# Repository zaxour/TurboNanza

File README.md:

# TurboNanza

***NOTE: I will provide support for Turbonanza if you purchased from:

My Ko-Fi Store: https://ko-fi.com/s/4d0de1c0ac
VideoGamePerfection (EU): https://videogameperfection.com/products/turbonanza-pcengine-turbografx/

If you purchased from AliExpress, I cannot provide support as it looks like they changed the design and did not publish the details.

***

[PC Engine Shuttle Installation Instructions](/images/shuttle/readme.md)

[PC Engine/Turbo Duo Installation Instructions](/images/duo/readme.md)

An internal RGB, S-Video, Composite video and Audio modification for the Turbografx 16, PCEngine and CoreGrafx. As of Revision C, support has been added for audio from the Turbo Everdrive Pro.

Design is KiCad format and all files necessary to open the design and have it fabricated are present within the archive.

Installation Method (WORK IN PROGRESS!!):

PINOUT (For reference/Non-Expansion-Port Installs):

## Step 1 - Remove the resistors for Luma, R-Y, B-Y, and Burst
### PC Engine & CoreGrafx

Remove resistors R134, R137, R138 and R156 

### TurboGrafx 16
Remove resistors R130-R132 and R134

### SuperGrafx
Remove resistors R164-167

## Step 2 - Disconnect CVBS pin from original circuit
### PC Engine & CoreGrafx
Remove resistor R145 (20 ohms)

### TurboGrafx 16
Remove resistor R127 (20 ohms)

### SuperGrafx
Remove resistor R147 

## Step 3 - Install TurboNanza
### PC Engine & CoreGrafx
Solder the TurboNanza over the expansion port pins as shown.

### TurboGrafx16
Solder the TurboNanza over the expansion port pins as shown.

### SuperGrafx
Prepare the flex cable by tinning the pads as shown.

Solder the TurboNanza to the flex cable as shown. It's recommended to verify continuity. Place some kapton/polyimide tape over the exposed solder pads on the bottom of the flex cable to avoid shorting to the shielding.

Solder the TurboNanza/Flex Cable combo over the expansion port pins as shown (ignore 4 wires at this time).

## Step 4 - Solder S-Video connections

**When soldering the Y/B-Y/R-Y/Burst wires, try to use as close to the exact same length of wire as possible to maintain proper phase shift!**

### PC Engine & CoreGrafx
Solder wires from the points shown to the pads on TurboNanza
(Do not remove R141, as previously directed. The Color Burst trace runs underneath and can easily sever. Leave R141 on and solder directly to the resistor pad)

### TurboGrafx 16
Solder wires from the points shown to the pads on TurboNanza

### SuperGrafx
Solder wires from the points shown to the pads on TurboNanza

## Step 5 - Attach the DIN to the main board
### PC Engine
Kits sold after 8/15/2023 now include a mounting board for the PCEngine. It is recommended to secure with two size M2 or 2-56 bolts/washers to allow for easy positioning.

Position the mount and loosely secure with screws/washers. The board may also be soldered - kapton/polyimide tape is recommended to position the board.

Place the DIN in the slot, and solder around the sides.

Solder the DIN FFC adapter to the DIN. Please make sure the "THIS SIDE TOP" text is visible before soldering, as it indicates which side is top.

### CoreGrafx
First, remove C162 (AC coupling capacitor for composite video - no longer necessary)

Scrape the solder mask off the copper on the left and right edges of the original DIN footprint as shown.

Solder the supplied mounting board to the mainboard.

Solder the DIN FFC adapter to the DIN. Please make sure the "THIS SIDE TOP" text is visible before soldering, as it indicates which side is top.

### TurboGrafx16
Solder the mounting board using the plated through holes for the RF modulator. Align the DIN on the mounting board such that it aligns with the console shell opening and solder in place.

### SuperGrafx
Remove the original DIN and scrape the soldermask approximately as shown.

Solder the mounting board as shown, aligning the center hole with the two ground through holes.

Mount the DIN and DIN board to the mount board.

## Step 6 - RF Shielding and Case trimming
### PC Engine
On the bottom shell of the case, trim the 2 ribs where the expansion port opening sits. Do not re-install the original shielding. If your PC Engine has shielding that has two tabs that solder close to the EXP port pins, you will need to run a wire to where the shielding originally terminated.

### CoreGrafx
Trim the RF shield such that the metal lip is not contacting the TurboNanza.

Like the PC Engine, trim the 2 ribs on the bottom shell where the expansion port opening is.

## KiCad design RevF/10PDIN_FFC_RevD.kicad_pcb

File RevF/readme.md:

Turbonanza Revision F

"DecaDIN" files are the smaller interface board meant for PC Engine and CoreGrafx consoles.

"10PDIN" is for all other systems

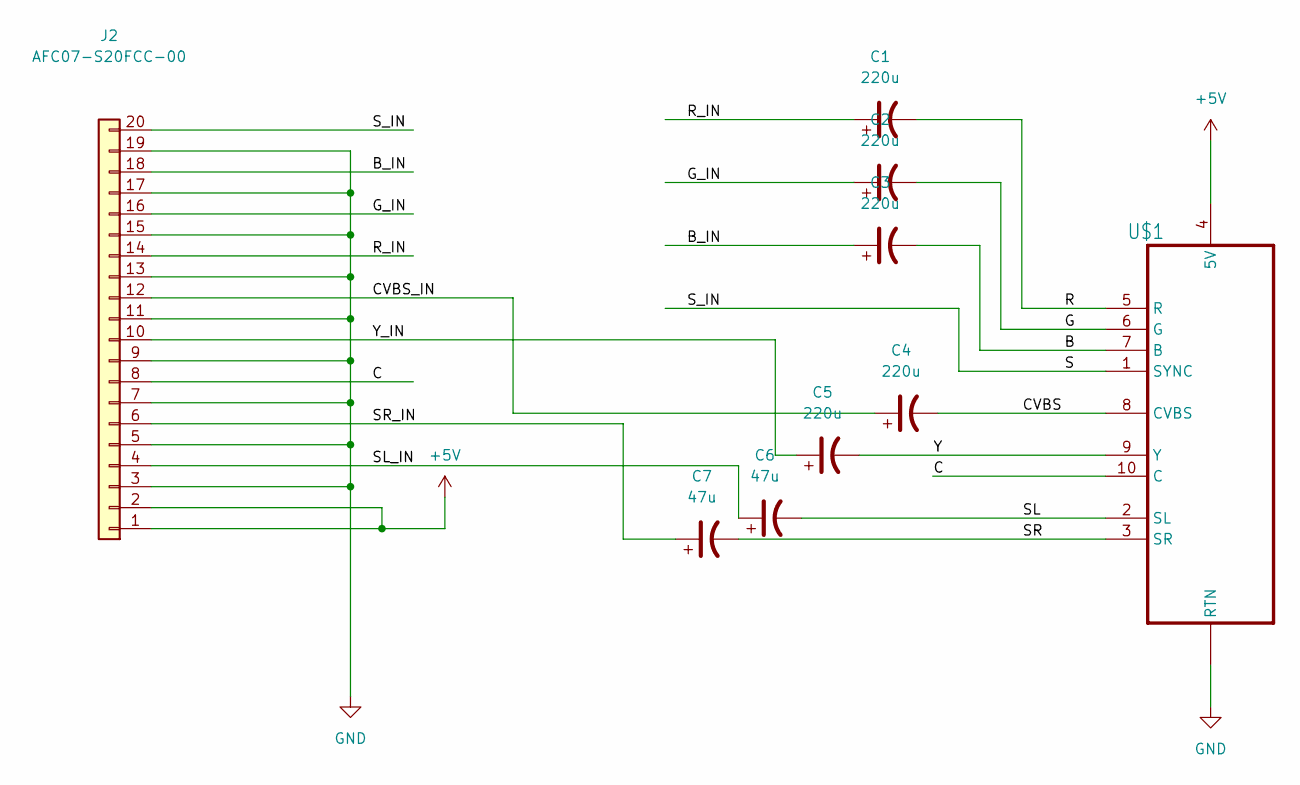
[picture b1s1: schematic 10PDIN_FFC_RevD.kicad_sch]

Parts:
C1, C2, C3, C4, C5: 220u; CP_EIA-3528-15_AVX-H
C6, C7: 47u; CP_EIA-3216-18_Kemet-A
J2: AFC07-S20FCC-00; Jushuo_AFC07-S20FCC-00
U$1: SATURN_10PDIN; CUI_MD-100SM

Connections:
+5V: J2.1, J2.2, U$1.4 (5V)
/B: C3.2, U$1.7 (B)
/B_IN: C3.1, J2.18
/C: J2.8, U$1.10 (C)
/CVBS: C4.2, U$1.8 (CVBS)
/CVBS_IN: C4.1, J2.12
/G: C2.2, U$1.6 (G)
/G_IN: C2.1, J2.16
/R: C1.2, U$1.5 (R)
/R_IN: C1.1, J2.14
/S: J2.20, U$1.1 (SYNC)
/SL: C6.2, U$1.2 (SL)
/SL_IN: C6.1, J2.4
/SR: C7.2, U$1.3 (SR)
/SR_IN: C7.1, J2.6
/Y: C5.2, U$1.9 (Y)
/Y_IN: C5.1, J2.10
GND: J2.3, J2.5, J2.7, J2.9, J2.11, J2.13, J2.15, J2.17, J2.19, U$1.S1 (RTN), U$1.S2 (RTN), U$1.S3 (RTN)

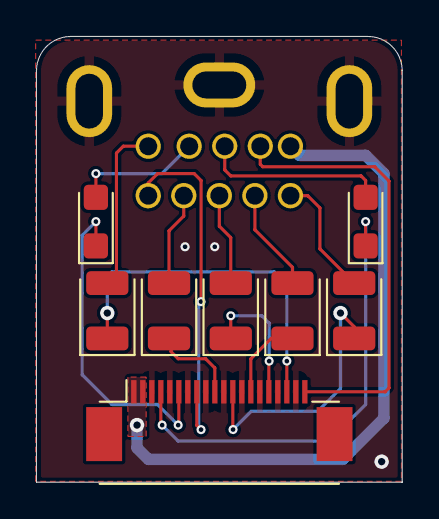
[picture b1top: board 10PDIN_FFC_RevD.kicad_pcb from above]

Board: 2 copper layers, 20.3 x 24.8 mm, 9 parts (1 on the bottom side), 18 nets.

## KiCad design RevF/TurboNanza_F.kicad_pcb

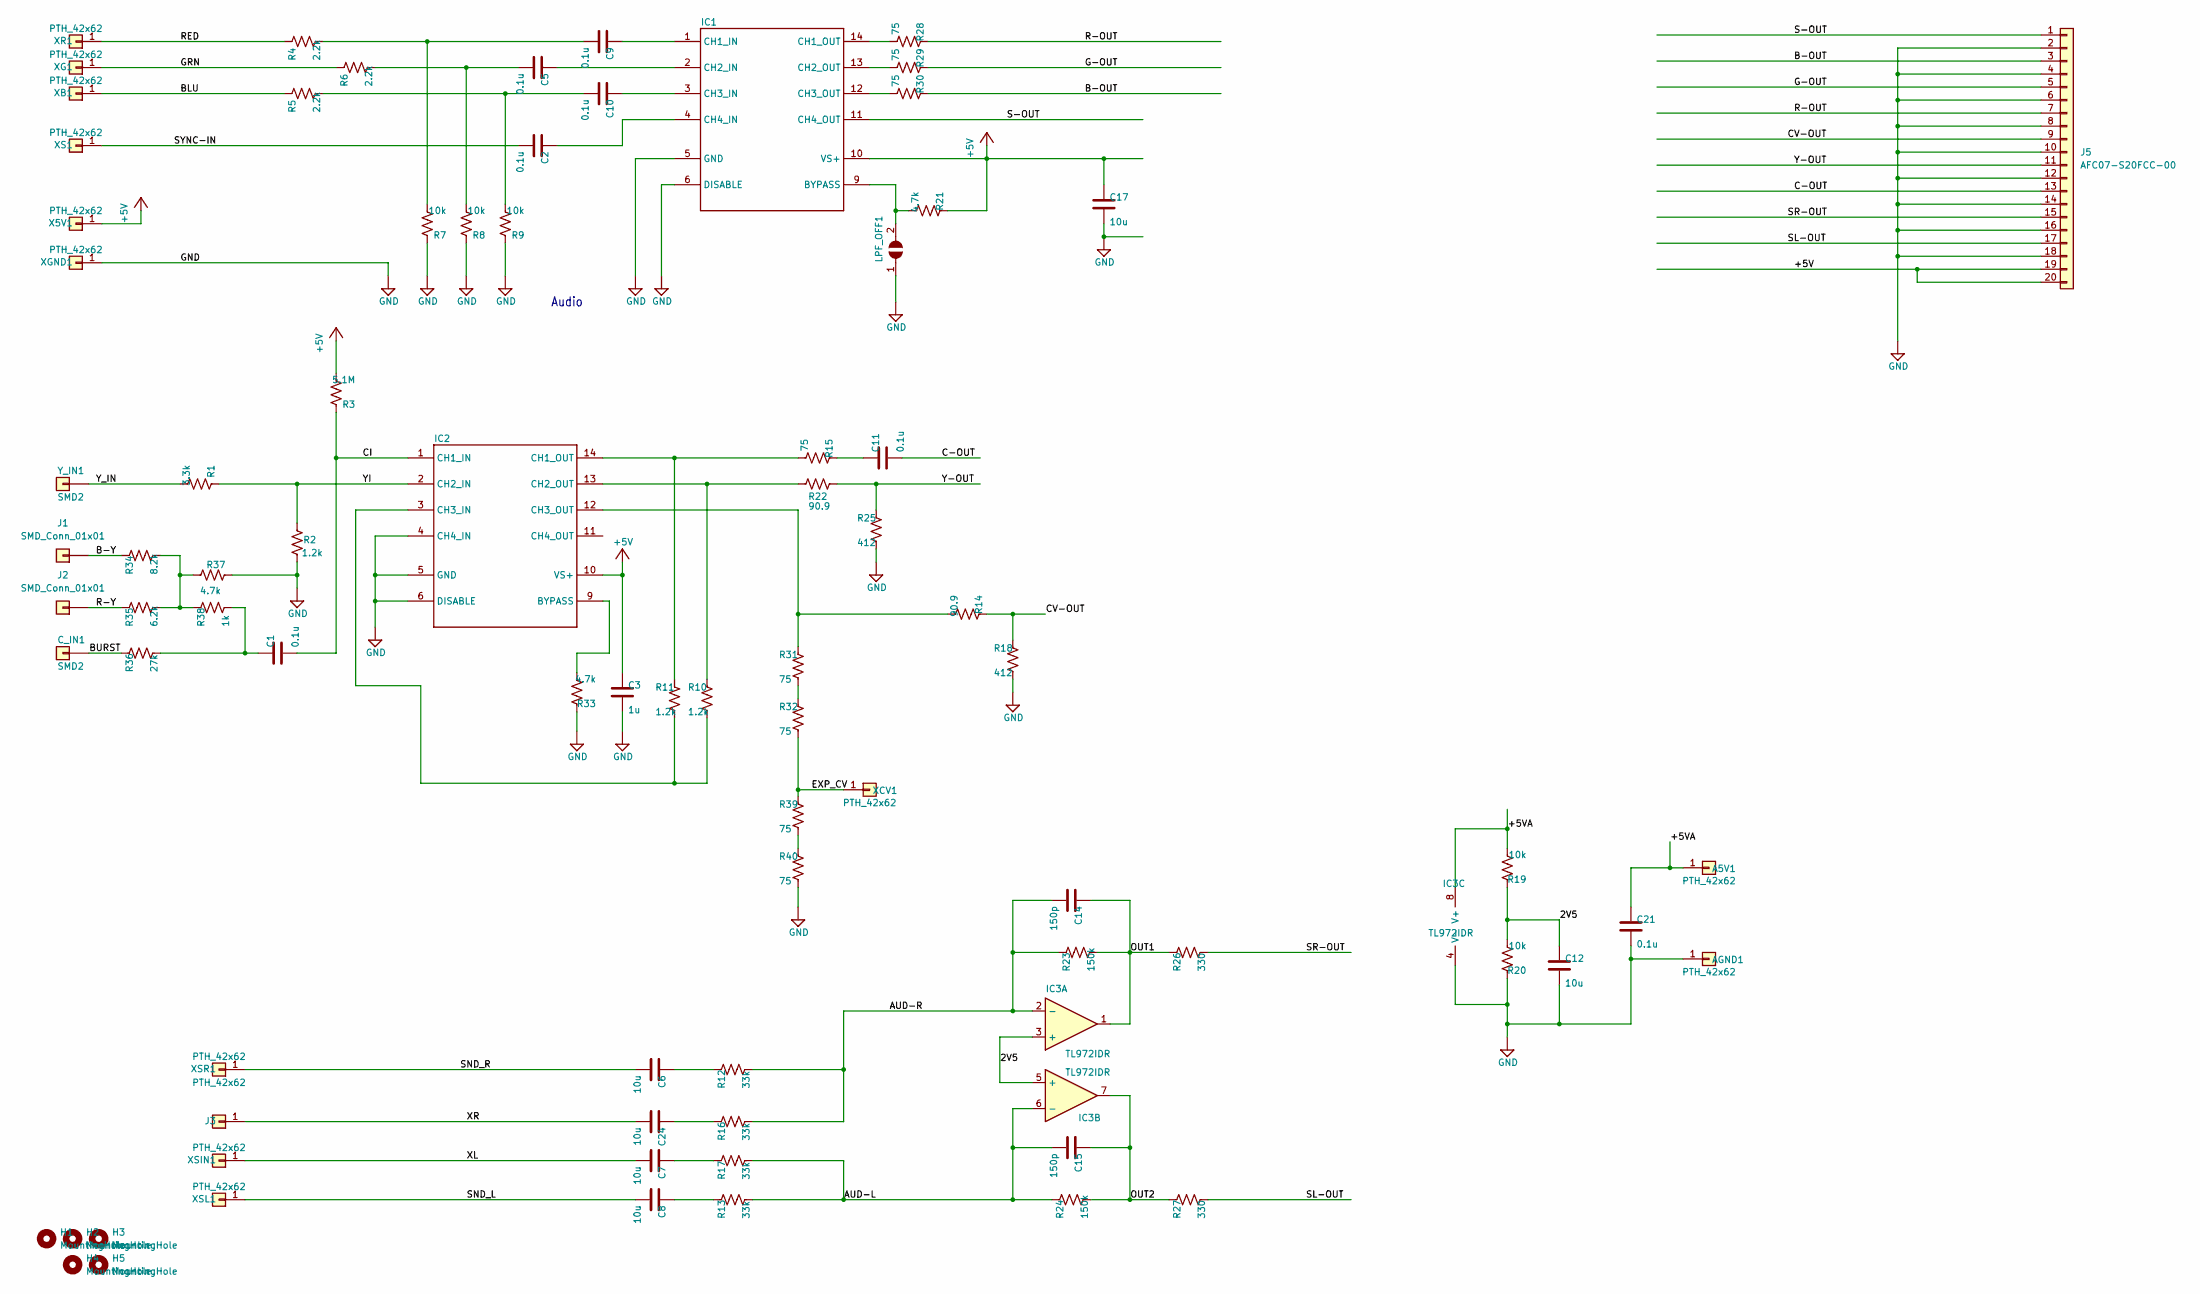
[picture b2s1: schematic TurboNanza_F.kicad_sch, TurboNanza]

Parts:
A5V1: PTH_42x62; Pin_D1.1mm
AGND1: PTH_42x62; Pin_D1.1mm
C1, C2, C5, C9, C10, C11, C21: 0.1u; C_0603_1608Metric
C3: 1u; C_0603_1608Metric
C6, C7, C8, C12, C17, C24: 10u; C_0805_2012Metric
C14, C15: 150p; C_0603_1608Metric
C_IN1: SMD2; SolderWirePad_1x01_SMD_1x2mm
H1, H2, H3, H4, H5: MountingHole; MountingHole_2.1mm
IC1, IC2: THS7374TSSOP14_LONG; TSSOP-14_4.4x5mm_P0.65mm
IC3: TL972IDR; SOIC-8_3.9x4.9mm_P1.27mm
J1, J2: SMD_Conn_01x01; SolderWirePad_1x01_SMD_1x2mm
J3: PTH_42x62; Pin_D1.1mm
J5: AFC07-S20FCC-00; Jushuo_AFC07-S20FCC-00
LPF_OFF1: SMD_J; SolderJumper-2
R1: 3.3k; R_0402_1005Metric
R2, R10, R11: 1.2k; R_0402_1005Metric
R3: 5.1M; R_0603_1608Metric
R4, R5, R6: 2.2k; R_0402_1005Metric
R7, R8, R9: 10k; R_0402_1005Metric
R12, R13, R16, R17: 33k; R_0603_1608Metric
R14, R22: 90.9; R_0402_1005Metric
R15, R28, R29, R30, R31, R32, R39, R40: 75; R_0402_1005Metric
R18, R25: 412; R_0402_1005Metric
R19, R20: 10k; R_0603_1608Metric
R21, R33: 4.7k; R_0402_1005Metric
R23, R24: 150k; R_0603_1608Metric
R26, R27: 330; R_0603_1608Metric
R34: 8.2k; R_0603_1608Metric
R35: 6.2k; R_0603_1608Metric
R36: 27k; R_0603_1608Metric
R37: 4.7k; R_0603_1608Metric
R38: 1k; R_0603_1608Metric
X5V1: PTH_42x62; Pin_D1.1mm
XB1: PTH_42x62; Pin_D1.1mm
XCV1: PTH_42x62; Pin_D1.1mm
XG1: PTH_42x62; Pin_D1.1mm
XGND1: PTH_42x62; Pin_D1.1mm
XR1: PTH_42x62; Pin_D1.1mm
XS1: PTH_42x62; Pin_D1.1mm
XSIN1: PTH_42x62; Pin_D1.1mm
XSL1: PTH_42x62; Pin_D1.1mm
XSR1: PTH_42x62; Pin_D1.1mm
Y_IN1: SMD2; SolderWirePad_1x01_SMD_1x2mm

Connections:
+5V: C3.1, C17.1, IC1.10 (VS+), IC2.10 (VS+), J5.19, J5.20, R3.2, R21.1, X5V1.1
/2V5: C12.1, IC3.3 (+), IC3.5 (+), R19.1, R20.2
/+5VA: A5V1.1, C21.1, IC3.8 (V+), R19.2
/AUD-L: C15.2, IC3.6 (-), R13.2, R17.2, R24.1
/AUD-R: C14.2, IC3.2 (-), R12.2, R16.2, R23.1
/B-OUT: J5.3, R30.1
/B-Y: J1.1, R34.1
/BLU: R5.1, XB1.1
/BURST: C_IN1.1, R36.1
/C-OUT: C11.2, J5.13
/CI: C1.2, IC2.1 (CH1_IN), R3.1
/CV-OUT: J5.9, R14.1, R18.1
/EXP_CV: R32.2, R39.1, XCV1.1
/G-OUT: J5.5, R29.1
/GRN: R6.1, XG1.1
/OUT1: C14.1, IC3.1, R23.2, R26.1
/OUT2: C15.1, IC3.7, R24.2, R27.1
/R-OUT: J5.7, R28.1
/R-Y: J2.1, R35.1
/RED: R4.1, XR1.1
/S-OUT: IC1.11 (CH4_OUT), J5.1
/SL-OUT: J5.17, R27.2
/SND_L: C8.2, XSL1.1
/SND_R: C6.2, XSR1.1
/SR-OUT: J5.15, R26.2
/SYNC-IN: C2.2, XS1.1
/XL: C7.2, XSIN1.1
/XR: C24.2, J3.1
/Y-OUT: J5.11, R22.1, R25.1
/YI: IC2.2 (CH2_IN), R1.1, R2.2
/Y_IN: R1.2, Y_IN1.1
GND: AGND1.1, C3.2, C12.2, C17.2, C21.2, IC1.5 (GND), IC1.6 (DISABLE), IC2.4 (CH4_IN), IC2.5 (GND), IC2.6 (DISABLE), IC3.4 (V-), J5.2, J5.4, J5.6, J5.8, J5.10, J5.12, J5.14, J5.16, J5.18, J5.MP, LPF_OFF1.1, R2.1, R7.1, R8.1, R9.1, R18.2, R20.1, R25.2, R33.1, R37.1, R40.2, XGND1.1
unnamed: C1.1, R36.2, R38.2
unnamed: C5.2, R6.2, R8.2
unnamed: C6.1, R12.1
unnamed: C7.1, R17.1
unnamed: C8.1, R13.1
unnamed: C9.2, R4.2, R7.2
unnamed: C10.2, R5.2, R9.2
unnamed: C11.1, R15.1
unnamed: C24.1, R16.1
unnamed: IC1.9 (BYPASS), LPF_OFF1.2, R21.2
unnamed: C9.1, IC1.1 (CH1_IN)
unnamed: IC1.14 (CH1_OUT), R28.2
unnamed: C5.1, IC1.2 (CH2_IN)
unnamed: IC1.13 (CH2_OUT), R29.2
unnamed: C10.1, IC1.3 (CH3_IN)
unnamed: IC1.12 (CH3_OUT), R30.2
unnamed: C2.1, IC1.4 (CH4_IN)
unnamed: IC2.9 (BYPASS), R33.2
unnamed: IC2.14 (CH1_OUT), R11.1, R15.2
unnamed: IC2.13 (CH2_OUT), R10.1, R22.2
unnamed: IC2.3 (CH3_IN), R10.2, R11.2
unnamed: IC2.12 (CH3_OUT), R14.2, R31.1
unnamed: R31.2, R32.1
unnamed: R34.2, R35.2, R37.2, R38.1
unnamed: R39.2, R40.1

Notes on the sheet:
Audio

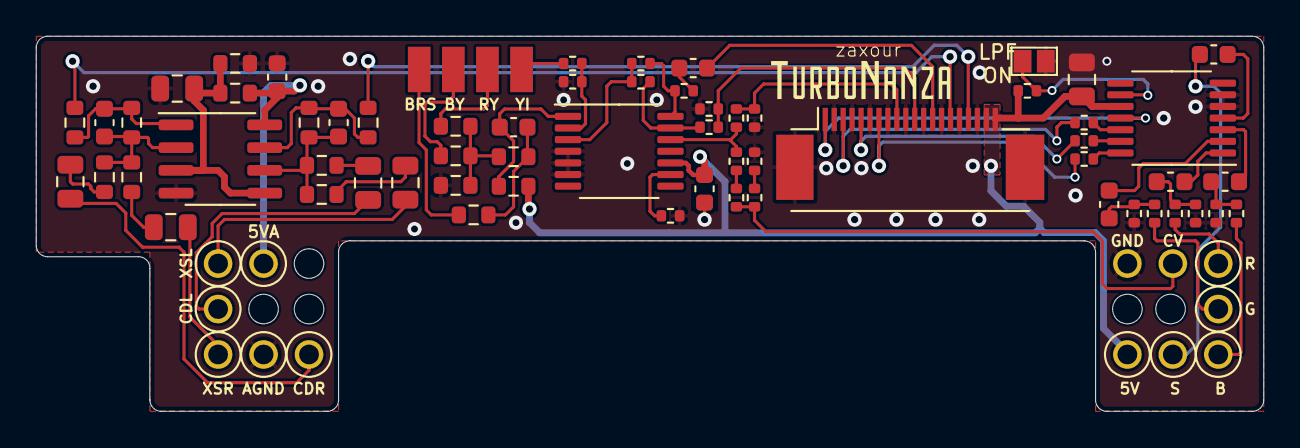
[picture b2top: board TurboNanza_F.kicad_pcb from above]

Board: 2 copper layers, 68.6 x 21.0 mm, 83 parts (0 on the bottom side), 57 nets.

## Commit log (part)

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2022-09-25 Add files via upload
    Replaced Eagle version with revised KiCad version
2023-02-17 Update README.md
    Updated with PC Engine Steps
2023-05-09 Update README.md
    Added admonishment about R141 on PCE/CG systems.
2023-05-12 Create LICENSE
2023-06-25 Update README.md
    Additional CoreGrafx handling instructions.
2023-08-15 Add files via upload
    PC Engine mounting board added
2023-08-28 Create readme.md
    Initial Duo instructions draft
2024-09-21 Update readme.md
    Forgot about resistor removal; not critical, but suggested to do so.
2025-04-20 Update README.md
    Updated PCE/CG Step 4 photo for clarity
2025-09-28 Update README.md
    Updated DIN mounting instructions for PCE/CG
2025-09-28 Update readme.md
    Updated Duo DIN and Audio instructions
